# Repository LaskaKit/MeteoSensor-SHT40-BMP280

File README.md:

# Module for atmospheric pressure and temperature and humidity measurement with BMP280 and SHT40

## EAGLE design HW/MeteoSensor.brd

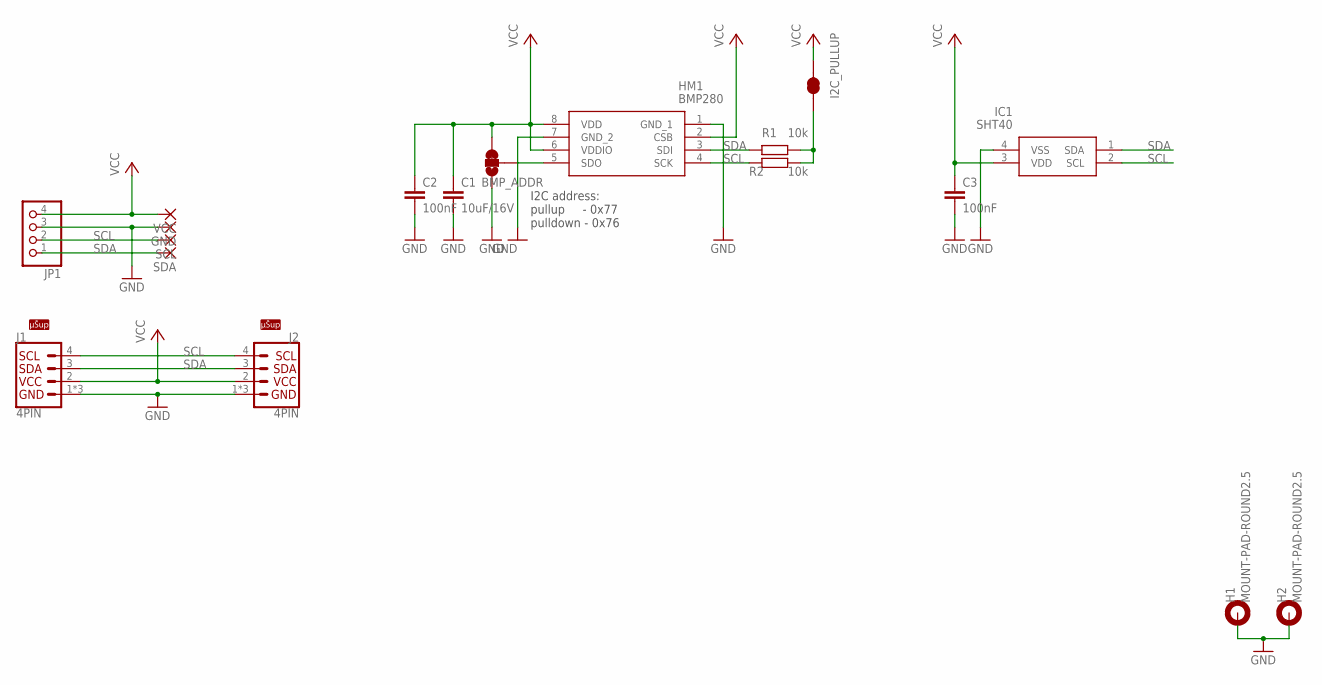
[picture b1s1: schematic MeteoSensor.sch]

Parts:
BMP_ADDR: JUMPER-SMT_3_1-NC_TRACE_NO-SILK; SMT-JUMPER_3_1-NC_TRACE_NO-SILK
C1: 10uF/16V; C0402
C2, C3: 100nF; C0402
GND: WIREPADSMD2,54-5,08; SMD2,54-5,08
H1, H2: MOUNT-PAD-ROUND2.5; 2,5-PAD
HM1: BMP280
I2C_PULLUP: JUMPER-SMT_2_NC_TRACE_NO-SILK; SMT-JUMPER_2_NC_TRACE_NO-SILK
IC1: SHT40
J1, J2: 4PIN; 1X04_1MM_RA
JP1: PINHD-1X4; 1X04
R1, R2: 10k; R0402
SCL: WIREPADSMD2,54-5,08; SMD2,54-5,08
SDA: WIREPADSMD2,54-5,08; SMD2,54-5,08
U$1, U$4: USUP_LOGO; USUP_4MM_SILKSCREEN
VCC: WIREPADSMD2,54-5,08; SMD2,54-5,08

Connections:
GND: BMP_ADDR.1, C1.2, C2.2, C3.2, GND.1, H1.1, H2.1, HM1.1 (GND_1), HM1.7 (GND_2), IC1.4 (VSS), J1.1 (GND), J1.NC1 (GND), J1.NC2 (GND), J2.1 (GND), J2.NC1 (GND), J2.NC2 (GND), JP1.3
unnamed: BMP_ADDR.2, HM1.5 (SDO)
unnamed: I2C_PULLUP.1, R1.2, R2.2
SCL: HM1.4 (SCK), IC1.2 (SCL), J1.4 (SCL), J2.4 (SCL), JP1.2, R2.1, SCL.1
SDA: HM1.3 (SDI), IC1.1 (SDA), J1.3 (SDA), J2.3 (SDA), JP1.1, R1.1, SDA.1
VCC: BMP_ADDR.3, C1.1, C2.1, C3.1, HM1.6 (VDDIO), HM1.8 (VDD), I2C_PULLUP.2, IC1.3 (VDD), J1.2 (VCC), J2.2 (VCC), JP1.4, VCC.1

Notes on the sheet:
I2C address: pullup - 0x77 pulldown - 0x76

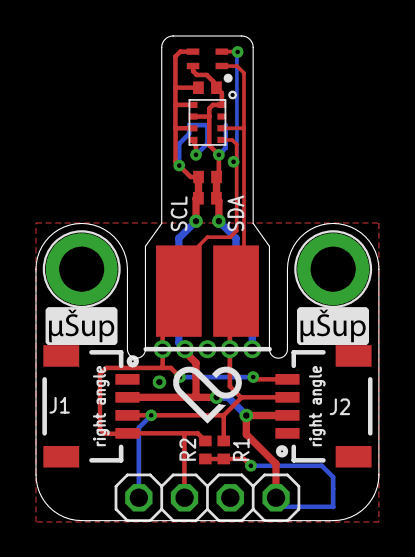
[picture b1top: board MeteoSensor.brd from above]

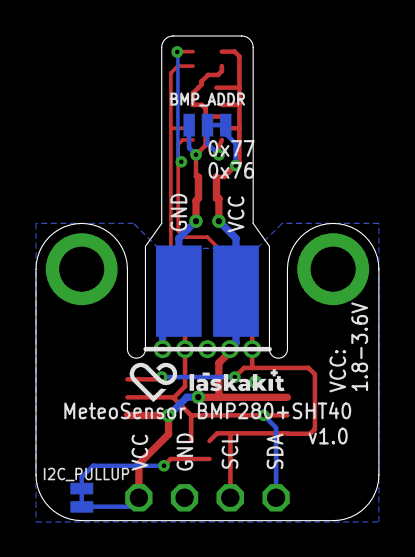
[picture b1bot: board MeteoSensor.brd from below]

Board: 2 copper layers, 19.1 x 26.9 mm, 22 parts (5 on the bottom side), 6 nets.

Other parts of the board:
U$2: LASKAKIT_HEART; LASKAKIT_HEART_4MM
U$3: LASKKIT_10MM_SILKSCREEN

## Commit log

2025-10-22 new ver
2025-12-22 delete
2026-04-21 pull-up resistors changed to 4.7k
2026-04-21 renamed

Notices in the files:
parts and their libraries:
LaskaKit-Jumpers: Licensing: Creative Commons ShareAlike 4.0 International - https://creativecommons.org/licenses/by-sa/4.0
